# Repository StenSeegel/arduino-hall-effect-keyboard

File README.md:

# Hall-Effect MIDI Keyboard

Ein hochperformanter MIDI-Controller auf Basis von Hall-Effekt-Sensoren und Arduino Leonardo.

## Kurzbeschreibung

Das Keyboard nutzt magnetische Sensoren für präzise Tastenabfragen und bietet fortschrittliche Funktionen für Musiker:

- **13 Hall-Effect Tasten**: Chromatischer Bereich (C-C) mit hoher Auflösung.
- **Intelligente Harmonik**: Echtzeit-Generierung diatonischer Akkorde in verschiedenen Skalen (Major, Minor, Kirchentonleitern etc.).
- **Phasen-Locked Arpeggiator**: Synchronisierte Sequenzen mit einstellbaren Mustern, Beat-Rates und Duty-Cycles.
- **Multifunktionales Interface**: 4 Funktionstasten zur Steuerung von Play-Modi (Hold/Additive) und Systemmenüs.
- **Visuelles Feedback**: Integriertes WS2812 LED-System für Status- und Performance-Anzeige.

## Dokumentation

- Detaillierte Bedienungsanleitung: [docs/MANUAL.md](docs/MANUAL.md)
- Informationen zum Akkord-System: [docs/CHORD_MODE_README.md](docs/CHORD_MODE_README.md)
- Architektur-Details: [docs/ARCHITECTURE.md](docs/ARCHITECTURE.md)

## Technische Features
- **Killall MIDI**: Sauberes Boot-Verhalten.
- **Input Quantization**: Präzises Timing bei Arpeggio-Einstiegen.
- **Low Latency**: Direkte Verarbeitung der Sensorwerte für latenzfreies Spiel.

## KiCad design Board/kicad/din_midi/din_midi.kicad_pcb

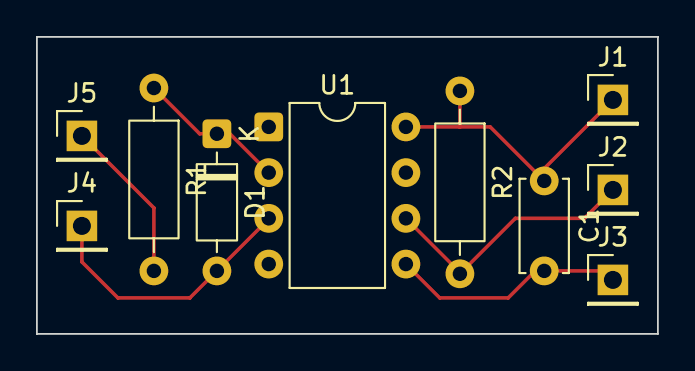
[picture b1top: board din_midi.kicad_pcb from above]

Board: 2 copper layers, 34.5 x 16.5 mm, 10 parts (0 on the bottom side), 6 nets.

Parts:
C1: 100nF; C_Disc_D5.0mm_W2.5mm_P5.00mm
D1: 1N4148; D_DO-35_SOD27_P7.62mm_Horizontal
J1, J2, J3, J4, J5: Conn_01x01; PinHeader_1x01_P2.54mm_Vertical
R1: 220R; R_Axial_DIN0207_L6.3mm_D2.5mm_P10.16mm_Horizontal
R2: 1K; R_Axial_DIN0207_L6.3mm_D2.5mm_P10.16mm_Horizontal
U1: 6N137; DIP-8_W7.62mm

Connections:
+5V: C1.1, J1.1, R2.1, U1.8 (VCC)
GND: C1.2, J3.1, U1.5 (GND)
unnamed: D1.2 (A), J4.1, U1.3 (C)
unnamed: D1.1 (K), R1.1, U1.2 (A)
unnamed: J2.1, R2.2, U1.6 (VO)
unnamed: J5.1, R1.2

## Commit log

2026-01-04 change pins for leonardo
2026-01-04 feat: implement midi interface
2026-01-06 feat: implement function switches for A1-A4
2026-01-07 feat: add chord mode
2026-01-08 feat: erweitere Button-Klasse um verbesserte Entprellung und Stabilitätsüberwachung
2026-01-08 feat: überarbeitete Akkord- und Skalenfunktionen
2026-01-08 refactor: Button-Klasse aufräumen
2026-01-08 feat: verbessere Trigger- und Release-Erkennung in der Button-Klasse
2026-01-08 feat: füge umfassende Bedienungsanleitung für das Hall-Effect Keyboard hinzu
2026-01-08 feat: diatonische Modi, non Scale Notes deaktiviert
2026-01-08 feat: überarbeitetes UI
2026-01-08 refactor: Halbtonberechnung für diatonische Modi
2026-01-08 feat: verbessere LED-Farben und füge Bootup-Animation hinzu
2026-01-09 feat: fix LED-Bestätigungsfarben, entferne Debug-Ausgaben
2026-01-09 feat: füge Unterstützung für Multi-Note Blink-Tracking hinzu
2026-01-09 feat: verschieben Oktavierung in Submenu, aktualisiere README
2026-01-10 refactor: Submodule für Teilfunktionalitäten, Arpeggiator hinzugefügt
2026-01-11 fix: Fehlerhafte Modi Kombinationen
2026-01-11 feat: aktualisiere LED-Farben im Submenu für bessere Sichtbarkeit
2026-01-18 feat: füge MIDI Clock Generator hinzu und synchronisiere Arpeggiator Start
2026-01-18 feat: MIDI Clock Input
2026-01-21 docs: midi in schematic and pcb
2026-01-23 docs: update schematic image
2026-01-23 docs: update midi in board
2026-01-23 docs: add gerber files
2026-01-26 feat: implement precise MIDI Clock synchronization and arpeggiator phase handling
2026-01-26 feat: enhance arpeggiator functionality with note clearing and play mode integration
2026-02-08 refactor: play mode system
2026-02-08 fix: update LED color for Arpeggiator Mode in documentation
2026-02-08 fix: optimize LED behavior in updateTapTempoLED function for better performance and visual feedback
2026-02-08 fix: increase held arpeggiator notes limit to 32 for better chord handling
2026-02-08 fix: update midiClockActive and related variables to volatile for proper ISR handling
2026-02-08 fix: remove unused octave LED functionality to streamline code
2026-02-08 refactor: reduce memory usage for efficiency
2026-02-08 feat: implement settings manager for EEPROM persistence and update documentation
2026-02-08 fix: ensure proper note release handling when hold mode is inactive
